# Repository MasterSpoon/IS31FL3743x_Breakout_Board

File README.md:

At present I have the PCB made and have them sitting on my desk but have not yet been able to test them. As far as I'm aware they should be fully functional but use them as your own risk. There is no warranty supplied or implied.

# IS31FL3743x Breakout Board

This ia a Dev board for the LUMISSIL Microsystems IS31FL3743A & IS31FL3743B LED drivers with the main difference being the A variant is I2C-1MHz and the B variant SPI-12MHz.

[IS31FL3743A datasheet](https://www.lumissil.com/assets/pdf/core/IS31FL3743A_DS.pdf)

[IS31FL3743B datasheet](https://www.lumissil.com/assets/pdf/core/IS31FL3743B_DS.pdf)

The are both 18 x 11 matrix drivers capable of supporting up to 198 LEDs / 66 RGB LEDs.
With an average current on each LED of 3.03mA they are suitable for SMD LEDs.
Eg. [Foshan NationStar Optoelectronics FM-B2020RGBA-HG ](https://lcsc.com/product-detail/Light-Emitting-Diodes-LED_Foshan-NationStar-Optoelectronics-FM-B2020RGBA-HG_C108793.html )

## Parts list

| Part | Package | Location | Notes |
|------|---------|----------|-------|
| ISSI Driver | UQFN-40(5x5) | U1 | IS31FL3743A or IS31FL3743B |
| 100nF Capacitor | 0603 | C1 & C2 | LED driver Capacitors |
| 1uF Capacitor | 0603 | C3 & C4 | LED driver Capacitors |
| 20ohm Resistor | 0805 | R1-R18 | Series Resistors for CS1-CS18 respectively |
| 10K Resistor | 0805 | R19 | ISET Resistor |
| 2K Resistor | 0805 | R20 & R21 | I2C pull up Resistors |

## General Notes

- In default configuration the breakout board is setup for the IS31FL3743A driver however if easily changed to suit the IS31FL3743B driver. 
- CSx Resistors have been listed as 20ohm, if using for RGB change the Resistors to 51ohm for the CSx channels that will be used for Red.
- SDB Pin is pulled high through the solder jumper, if wanting to control through MCU cut the jumper trace and solder a wire to the pad above the S Pin on the SDB solder jumper.

## IS31FL3743A Notes

- I2C Pullup Resistors are connected to VCC, if using an MCU that is not 5V tollerant will need to omit R20 & R21 and provide pullup Resistors elsewhere.
- I2C address default has ADDR1 & ADDR2 Pulled to GND. Solder jumpers can be used to change if required.
    - GN1VC Sets ADDR1 between GND and VCC, 514 sets ADDR1 between Pin 5(SCL) & Pin 4(SDA).
    - GN2VC Sets ADDR2 between GND and VCC.
    - **WARNING** Before setting any solder jumpers cut the jumper trace for the ADDR Pin first.
    - Note : Not all address combinations have been made available through solder jumpers. 

## IS31FL3743B Notes

- Omit R20 & R21 Resistors as these are for I2C Pullups and will pull MOSI & SCL Pins high.
- Cut the solder bridge traces for GN1VC & GN2VC to avoid the CS and MISO Pins being pulled to GND.
- Silkscreen is based on IS31FL3743A driver. Differences for IS31FL3743B are

| Silkscreen | Function |
|------------|----------|
| SDA | MOSI |
| SCL | SCK |
| A1 | CS |
| A2 | MISO |

## Board Size

The board has been designed to be compatible with a standard 2.54mm breadboard. It has two rows of 18x2.54mm pins spaced 7x2.54mm (17.78mm) apart. There are two M3 mounting holes spaced 38mm apart but with a 3mm offset due to limited space. Both holes are equally 19mm from board centre however the top hole near the solder jumpers is 1mm to the right with the bottom hole 2mm to the left.

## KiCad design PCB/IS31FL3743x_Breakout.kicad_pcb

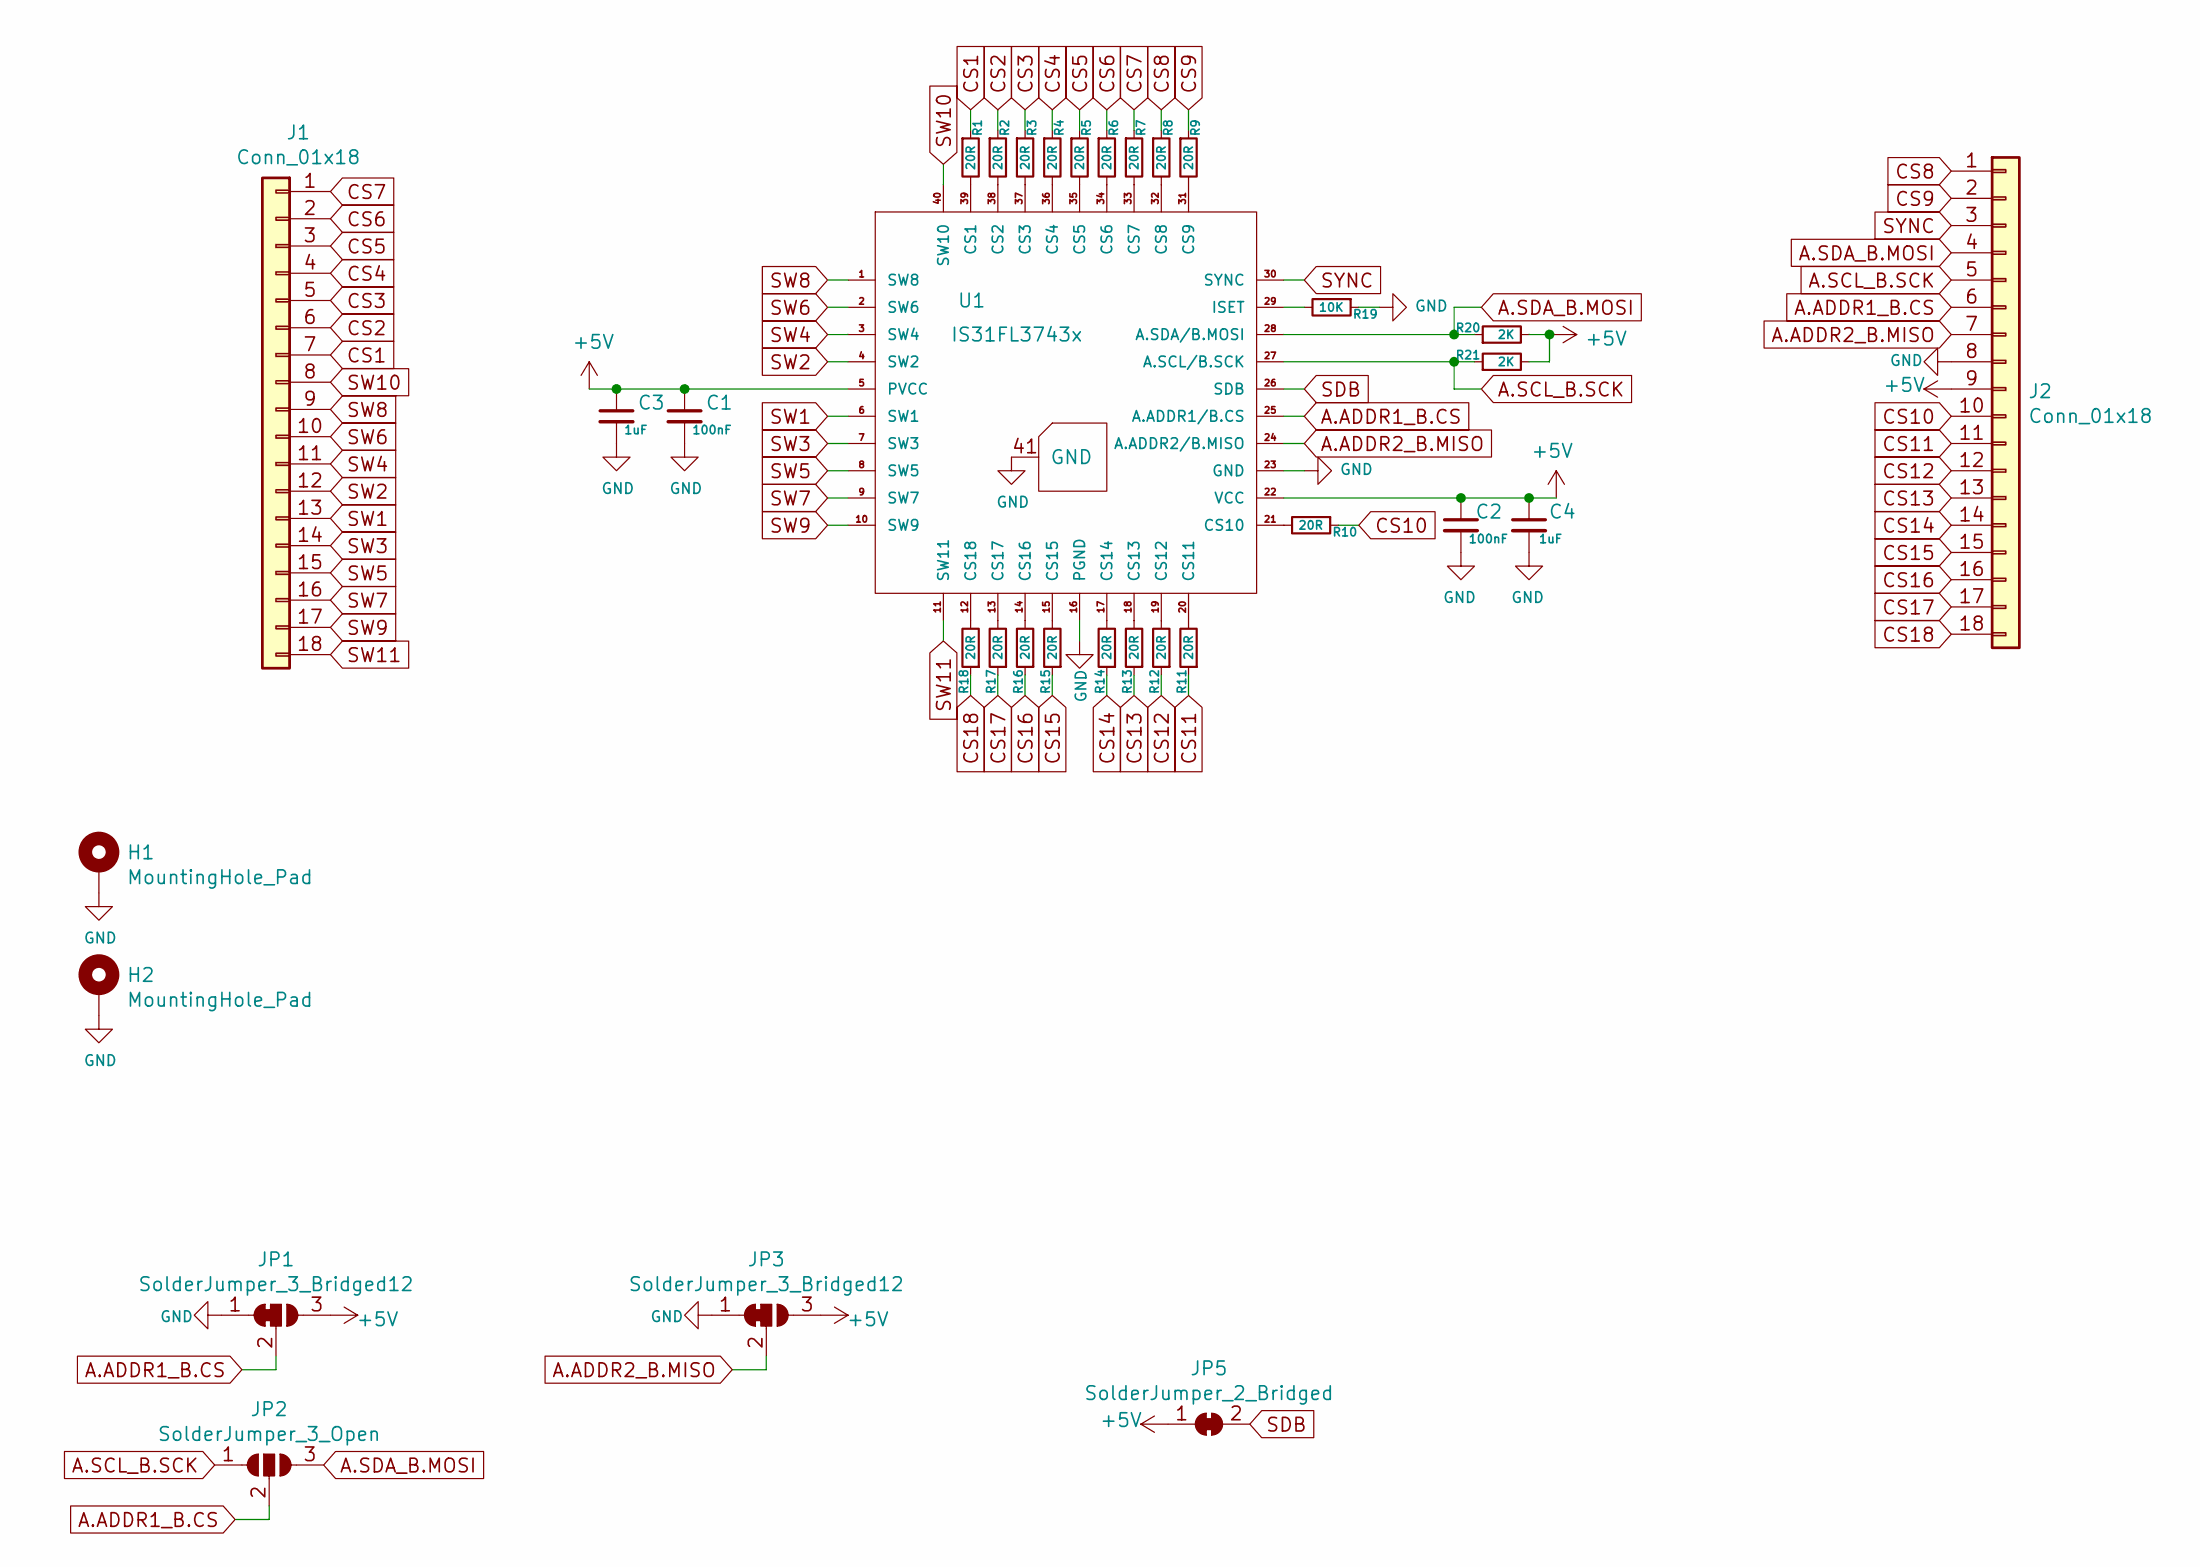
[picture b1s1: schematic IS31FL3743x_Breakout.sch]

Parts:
C1, C2: 100nF; C_0603_1608Metric
C3, C4: 1uF; C_0603_1608Metric
H1, H2: MountingHole_Pad; MountingHole_3.2mm_M3
J1, J2: Conn_01x18; PinHeader_1x18_P2.54mm_Vertical
JP1, JP3: SolderJumper_3_Bridged12; SolderJumper-3_P1.3mm_Bridged12_RoundedPad1.0x1.5mm
JP2: SolderJumper_3_Open; SolderJumper-3_P1.3mm_Open_RoundedPad1.0x1.5mm
JP5: SolderJumper_2_Bridged; SolderJumper-2_P1.3mm_Bridged_RoundedPad1.0x1.5mm
R1, R2, R3, R4, R5, R6, R7, R8, R9, R10, R11, R12, R13, R14, R15, R16, R17, R18: 20R; R_0805_2012Metric
R19: 10K; R_0805_2012Metric
R20, R21: 2K; R_0805_2012Metric
U1: IS31FL3743x; QFN-40-IS31FL3743A_extended

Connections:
+5V: C1.1, C2.1, C3.1, C4.1, J2.9, JP1.3 (B), JP3.3 (B), JP5.1 (A), R20.2, R21.2, U1.5 (PVCC), U1.22 (VCC)
A.ADDR1_B.CS: J2.6, JP1.2 (C), JP2.2 (C), U1.25 (A.ADDR1/B.CS)
A.ADDR2_B.MISO: J2.7, JP3.2 (C), U1.24 (A.ADDR2/B.MISO)
A.SCL_B.SCK: J2.5, JP2.1 (A), R21.1, U1.27 (A.SCL/B.SCK)
A.SDA_B.MOSI: J2.4, JP2.3 (B), R20.1, U1.28 (A.SDA/B.MOSI)
CS1: J1.7, R1.1
CS2: J1.6, R2.1
CS3: J1.5, R3.1
CS4: J1.4, R4.1
CS5: J1.3, R5.1
CS6: J1.2, R6.1
CS7: J1.1, R7.1
CS8: J2.1, R8.1
CS9: J2.2, R9.1
CS10: J2.10, R10.1
CS11: J2.11, R11.1
CS12: J2.12, R12.1
CS13: J2.13, R13.1
CS14: J2.14, R14.1
CS15: J2.15, R15.1
CS16: J2.16, R16.1
CS17: J2.17, R17.1
CS18: J2.18, R18.1
GND: C1.2, C2.2, C3.2, C4.2, H1.1, H2.1, J2.8, JP1.1 (A), JP3.1 (A), R19.1, U1.16 (PGND), U1.23 (GND), U1.41 (GND)
unnamed: R1.2, U1.39 (CS1)
unnamed: R2.2, U1.38 (CS2)
unnamed: R3.2, U1.37 (CS3)
unnamed: R4.2, U1.36 (CS4)
unnamed: R5.2, U1.35 (CS5)
unnamed: R6.2, U1.34 (CS6)
unnamed: R7.2, U1.33 (CS7)
unnamed: R8.2, U1.32 (CS8)
unnamed: R9.2, U1.31 (CS9)
unnamed: R10.2, U1.21 (CS10)
unnamed: R11.2, U1.20 (CS11)
unnamed: R12.2, U1.19 (CS12)
unnamed: R13.2, U1.18 (CS13)
unnamed: R14.2, U1.17 (CS14)
unnamed: R15.2, U1.15 (CS15)
unnamed: R16.2, U1.14 (CS16)
unnamed: R17.2, U1.13 (CS17)
unnamed: R18.2, U1.12 (CS18)
unnamed: R19.2, U1.29 (ISET)
SDB: JP5.2 (B), U1.26 (SDB)
SW1: J1.13, U1.6 (SW1)
SW2: J1.12, U1.4 (SW2)
SW3: J1.14, U1.7 (SW3)
SW4: J1.11, U1.3 (SW4)
SW5: J1.15, U1.8 (SW5)
SW6: J1.10, U1.2 (SW6)
SW7: J1.16, U1.9 (SW7)
SW8: J1.9, U1.1 (SW8)
SW9: J1.17, U1.10 (SW9)
SW10: J1.8, U1.40 (SW10)
SW11: J1.18, U1.11 (SW11)
SYNC: J2.3, U1.30 (SYNC)

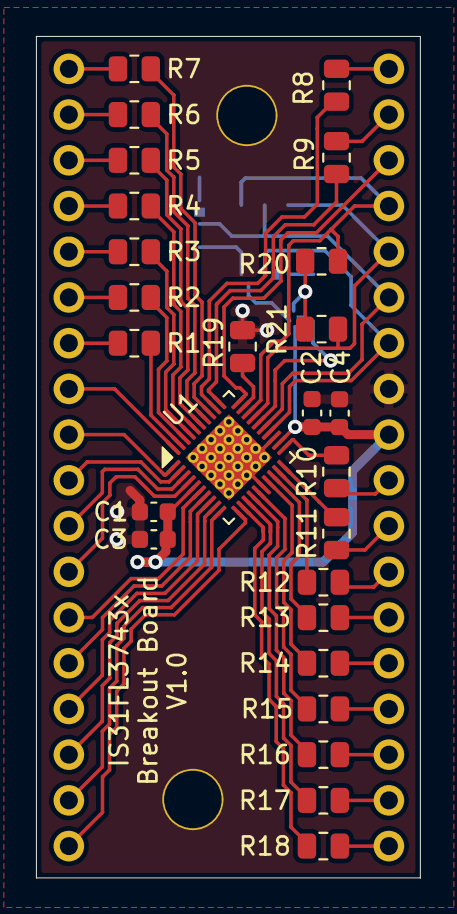
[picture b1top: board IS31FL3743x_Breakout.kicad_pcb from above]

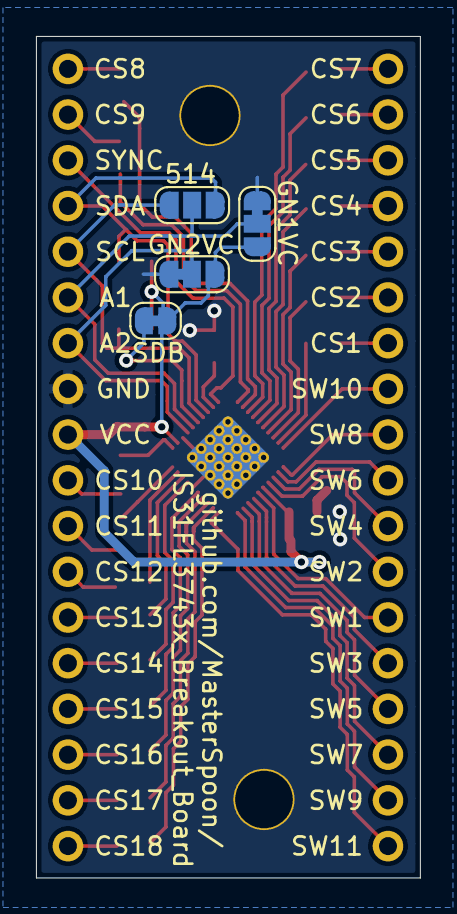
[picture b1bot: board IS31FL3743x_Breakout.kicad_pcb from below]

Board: 2 copper layers, 21.3 x 46.8 mm, 34 parts (4 on the bottom side), 56 nets.

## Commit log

2021-11-16 Add board files
2021-11-16 Updated docs
2021-11-16 Fixed typos
2021-11-16 Typos
2021-11-16 add renders and gerbers
2021-11-16 Documentation
2021-11-16 link
2021-11-30 regenerate gerbers
